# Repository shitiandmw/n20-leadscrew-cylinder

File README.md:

# n20-leadscrew-cylinder

**A 3D-printable linear actuator for a model excavator that looks like a hydraulic cylinder.** It is driven by a standard N20 gearmotor with an integrated M3 leadscrew, used exactly as bought. That is the actuator_v5 design described below; the current [two-wire V6](actuator_v6/README.md) (rev 6.2) uses the 12 V 1:50 N20 with an M4 × 0.7 leadscrew.

**The [complete X1 excavator](excavator_complete/README.md) puts the current revision of every subsystem together.** It combines:
- the J9 tracks and the X1 revision F X-frame;
- the RU66 slewing ring and the R3 turntable;
- body B1 rev B with the main board rev B (all seven motor drivers on the 12 V battery);
- the R12 arm.

It has an offline 3D demonstration with a scripted work cycle (travel, dig, swing, dump), the assembly order, an exploded view, layer-by-layer structure and the harness. Whole-machine checks cover clashes, the swing envelope, static balance, every cable's route over the arm's poses and the assembly moves that only exist on the combined machine. R12 sits on a new adapter, B01X, which replaces the ARM60 base on the turntable and now carries the arm cables. The folder also holds the whole machine's [wiring](excavator_complete/WIRING.md), [connector catalogue](excavator_complete/CONNECTORS.md) (every connector by type and model, with realistic models and a [gallery](excavator_complete/connector_gallery.html)), [standard parts and where they sit](excavator_complete/STANDARD_PARTS.md), [parts list](excavator_complete/BOM.md), [installation sequence](excavator_complete/ASSEMBLY.md) (animated in the viewer) and the [control circuit check](excavator_complete/CONTROL_CHECK.md).

The latest lower chassis is [X1 revision F with J9 tracks](track_wheel_jgy370/X1/README.md). Each X-frame leg ends in a curved support seated in a shallow recess in the track's main plate, clamped by two M4 screws through plain holes with the washers and nuts outside the plastic. The idler spring is enclosed in a bore in the track's main web and guided by a sliding piston. See the [revision notes](track_wheel_jgy370/X1/REV_F_NOTES.md) for the matched parts, assembly order and validation scope. To build the two tracks, start with the [track kit](track_wheel_jgy370/J9/TRACK_KIT.md): every file to print, every standard part to buy, the tools, an offline [installation animation](track_wheel_jgy370/J9/install_animation.html) that fits the parts step by step, and a [parts showcase](track_wheel_jgy370/J9/parts_showcase.html) to look at each part in 3D with its dimensions and material.

The [Sand / Lab application](excavator_app/README.md) turns the complete X1 / J9 / R12 machine into a Docker-deployable digging sandbox, with the R12 bucket's own profile doing the digging. A desktop displays the complete CAD assembly and a live sand yard: a deformable sand bed that slumps to its angle of repose, a load in each bucket that heaps up to the bucket's rated heaped capacity and slides off when the bucket is tipped, and falling sand wherever it spills or pours; a phone pairs by QR code and controls the boom, stick, bucket, slew and tracks over WebSocket. It includes touch joysticks, keyboard controls, emergency stop, connection watchdogs, and verified scoop-and-pour physics. Run `docker compose up --build -d` from `excavator_app/` to start it.

The [complete tracked arm60 excavator](excavator_60mm/README.md) adds independent track drives, steel-pinned links, sprung idlers, bearing-supported geared slewing and a recessed slew cover around the existing 60 mm arm. Its R3 upper body follows the Cat 320 layout: cab front-left, tank housing and stepped toolbox front-right, an engine hood with a battery hatch, and a curved counterweight on the 189 mm tail-swing radius holding steel ballast. Two 18650 cells sit in a cradle sized from manufacturer datasheets. Track R4 adds Berco-referenced sprockets engaging steel bushings, rollers with two outer guide flanges, and a 394 mm track stance around the 308 mm upper platform. Offline playback shows the loaded contact simulation, including passive wheel rotation, idler take-up, forward/reverse travel and braking. The preview allows independent boom and slew travel; track clearance is managed by the operator. Its folder includes parametric CAD, printable parts, a complete STEP assembly, an offline preview, mechanical assembly instructions and reproducible geometry, load and physics simulations. Physical fit, powered operation and payload still require prototype testing.

The [R10 arm with two boom actuators and a deeper boomerang profile](excavator_arm_dual/README.md) implements the user's latest revision: symmetric boom drives at Y = ±50 mm and a hollow, tapered boom with a 76.7 mm middle section, retaining the original joint coordinates and five replaceable teeth. All four actuators are modeled independently. Fixed-base rigid-body simulations track both unloaded and 150 g cycles under an assumed 100 N limit per drive; each boom drive peaks at 58.4 N with the example load. CAD, printable parts, assembly instructions, an offline viewer and a 54-second motion video are included. A feedback-offset case demonstrates unequal load sharing; hardware synchronization, structural strength and soil interaction remain unverified.

R6–R9 and their motion-review files have been removed from the workspace at the user's request. The current arm is R10 in `excavator_arm_dual/`, with actuator dependencies in `actuator_v6/`. Earlier tracked designs remain in Git history. The complete vehicle and sandbox still use the earlier ARM60 model; R10 has not been integrated into them.

The 1:12 ground-mounted arm (`excavator_arm/`, with its V6-T/B/K actuators) and the J8 track at the top of `track_wheel_jgy370/` were removed on 2026-11-12 because nothing current used them. They remain in Git history; for example, commit `39bc9a7` has both.

A separate [60 mm stroke edition](excavator_arm_60mm/README.md) uses four identical actuators and smaller 1:15 proportions: 380 mm boom, 193.3 mm stick and 80 mm bucket. Its [offline preview](excavator_arm_60mm/3D_preview.html), CAD and drawings are kept in their own folder. Its actuator, V6-U60, is one of the three lengths (V6-S, V6-U60, V6-L) of the general-purpose [two-wire V6 actuator](actuator_v6/README.md). The current R4 model integrates the upper lift mounts into broad supports on the boom, with thicker cheeks and a shared steel cross-pin.

The motor's own leadscrew drives a brass nut inside the rod. Two Hall-effect end stops hide in a covered channel along the barrel. A small controller blocks each direction in hardware once that end is reached.

The geometry, STL/STEP files, wire routes, schematic and a self-contained 3D preview are all generated from parametric Python (CadQuery).

> **Status:** the design is complete and checked in CAD, but it has not been printed or powered yet. See [Status](#status).

## Features

- **Unmodified N20 leadscrew motor.** There is no coupler, bearing or separate screw. The brass M3 nut in the rod's carrier rides directly on the motor's screw. The gearbox seats on a step in the barrel and the rear cap backs the motor can.
- **Hydraulic-cylinder look:**
  - a round Ø21 mm yellow barrel;
  - Ø23 mm graphite end caps, with a wiper lip at the rod end;
  - a Ø9 mm chrome-look rod;
  - Ø14 mm clevis eyes for Ø3 mm pins;
  - a hose-style cable port with a TPU boot.
- **Hidden end stops.** Two DRV5033AJ Hall sensors sit in a dovetail channel under a flush cover strip, along with their resistors, capacitors and wiring. Each sensor slides ±3 mm for calibration.
- **Hardware direction gating.** A 74HC08 blocks motion toward an end as soon as that end's sensor trips, regardless of the firmware. The Arduino adds a current trip (ACS712), a 30 s run timeout and latching faults.
- **Parametric.** Change the leadscrew length and the stroke, barrel, rod, sensor positions, cover strip and wire routes all follow.
- **Self-checking outputs.**
  - The CAD build checks for interference over the full stroke, checks that every wire lands on its terminal, and checks that every STL is watertight.
  - The schematic generator rebuilds the connections from the drawing itself. It compares them with the netlist and with the firmware's pin constants.

## Specifications

Default build, for a 40 mm leadscrew:

| | |
|---|---|
| Stroke | 30 mm, plus 2 / 3 mm mechanical over-travel at retract / extend |
| Pin centres | 108 mm retracted → 138 mm extended |
| Barrel | Ø21 × 76 mm, end caps Ø23 mm |
| Rod | Ø9 mm |
| Clevis eyes | Ø14 mm, 10.4 mm thick, Ø3.2 mm holes |
| Motor | N20 gearmotor (10 × 12 mm body) with integrated M3 × 0.5 leadscrew |
| End stops | 2 × TI DRV5033AJQLPG and an N35 Ø4 × 2 mm magnet |
| Electronics | 6 V motor supply, 5 V logic: DRV8833, ACS712-05B, SN74HC08, Arduino Nano |

A longer screw gives a longer stroke. For example, a 60 mm screw gives 50 mm of stroke and 128 → 178 mm pin centres. See the [full table](actuator_v5/README.md#rebuild).

## A look inside

The left image is a section on the pin plane, showing the motor, leadscrew, brass nut in the rod's carrier, and magnet. The right image shows the sensor channel with the cover strip removed.

For an interactive view, download [`actuator_v5/3D_preview.html`](actuator_v5/3D_preview.html) and open it in any browser. It is a single 7 MB file that works offline; GitHub can't run it in the page. The preview includes:

- exterior, section, wiring and core-part views;
- a stroke slider;
- a live demo of the end stops and the overcurrent trip.

## Electronics

| Sheet 1: inside the actuator | Sheet 2: controller board |
|---|---|
|  |  |

- Full schematic: [`schematic.pdf`](actuator_v5/electronics/schematic.pdf) (A3).
- Harness, pin tables and commissioning: [`wiring.md`](actuator_v5/electronics/wiring.md).
- Firmware: [`actuator_protection.ino`](actuator_v5/electronics/actuator_protection/actuator_protection.ino).

## Repository layout

```
actuator_v5/
├── README.md           build guide: print settings, assembly order, calibration, rebuild
├── BOM.md              everything to buy, with reference designators
├── 3D_preview.html     offline interactive 3D viewer
├── stl/                printable parts (PETG); soft/ = TPU boot; fit_samples/ = test slices
├── step/               single parts plus the full assembly with wiring
├── electronics/        schematic, netlist, wiring.md, Arduino sketch, logic tests
├── images/             renders and analysis plots
├── references/         motor drawing and photo the design is based on
├── parameters.json     key dimensions of the current build
├── validation.json     geometric check report
└── source/             generators (CadQuery, schemdraw, Blender, three.js viewer)
```

## Building one

1. **Measure your leadscrew** from the gearbox front face to the tip. If it is not 40 mm, rebuild with `--screw-length` (see below).
2. **Print** the parts in `actuator_v5/stl/` in PETG and the boot in `stl/soft/` in TPU 95A. Print the four fit samples first.
3. **Buy** the parts in [`BOM.md`](actuator_v5/BOM.md).
4. **Assemble, wire and calibrate** by following the [build guide](actuator_v5/README.md#assembly-order). Check the motor direction first. Then set each Hall sensor so that it stops the motor just before the mechanical stop.

## Rebuilding from source

Tested with Python 3.11 and the packages in [`requirements.txt`](actuator_v5/source/requirements.txt) (CadQuery 2.8, trimesh, schemdraw, matplotlib, ReportLab, PyMuPDF). The renders need Blender 4.2.

```sh
cd actuator_v5
pip install -r source/requirements.txt
python source/build_v5.py --screw-length 40         # STEP/STL, meshes, validation (about 3 minutes)
python source/magnet_trigger.py                     # magnet model and Hall placement
python source/build_schematic.py                    # schematic, plus connectivity and firmware checks
python source/build_viewer.py                       # 3D_preview.html
blender -b -P source/render_v5.py -- --out images   # optional renders
```

`build_v5.py` stops with an error if any geometric check fails.

The logic tests need no hardware (run them from `actuator_v5/` too):

```sh
python electronics/check_direction_gates.py         # 74HC08 gates: all 16 input states
c++ -std=c++17 -UNDEBUG electronics/protection_logic_test.cpp -o /tmp/protection_test && /tmp/protection_test
```

## Status

Checked:

- **CAD** (results in [`validation.json`](actuator_v5/validation.json)):
  - no interference between parts, hardware and wires anywhere in the stroke;
  - all eight wires land on their terminals;
  - wire routes still clear with each sensor moved ±3 mm;
  - every STL is watertight.
- **Electronics:**
  - the schematic's connections match the netlist and the firmware's pin map;
  - the 74HC08 truth table passes;
  - the protection-logic unit test passes;
  - the Arduino sketch compiles against a stub of the Arduino API.

Not verified yet:

- printing and fit;
- the real motor's ratings, the gearbox's axial load capacity and PETG creep under load;
- magnetic switching on real parts (the magnet model ignores the steel screw and nut);
- the firmware running on a board.

The current trip (550 mA for 150 ms) is a starting value. Set it against the real motor during commissioning.

To do:

- the remaining renders (stroke positions and close-ups);
- an illustrated assembly guide PDF.

## License

No license has been chosen yet. The bundled three.js is MIT-licensed (see [`THREE_LICENSE.txt`](actuator_v5/source/vendor/THREE_LICENSE.txt)).

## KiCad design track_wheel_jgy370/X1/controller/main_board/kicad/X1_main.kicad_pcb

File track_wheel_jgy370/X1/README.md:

# X1 revision F — straight arms seated in the track main beam

Each X101 arm runs straight at its full 28 mm width into the track main plate and ends flat in a plain 1.5 mm recess. The deck and the arched underside are single smooth curves. One screw on each side of the arm's centre web clamps the joint through plain holes; the heads and washers sit in side slots under the closed deck, and the rear washers and nuts are external. The accepted enclosed spring guide is retained.

The R3 turntable sits on the RU66 seat, and the upper body B1 rev B sits on it. The body is traced from the Cat 320: three main prints (counterweight, left half with the cab, right half with the tank), four small ones, and the 18650 battery on the swing centreline under a lift-off hatch. Rev B issue 2 (2026-11-07) adds a cable notch in each half's inboard hood wall for the arm harness of the complete machine (`excavator_complete/WIRING.md`). See [TURNTABLE.md](TURNTABLE.md) and [BODY.md](BODY.md).

**Control system: spec C1 issue 4; main board rev B designed (schematic, PCB and firmware).**
- The main board (rev B) sits in the left bay: ESP32-S3, 7 × DRV8876 on the battery, 5 V / 3.3 V rails, lamps, buzzer and an expansion header. Its motor, lamp and expansion headers are top entry since 2026-11-14, so the plugs go on from above.
- Its KiCad 9 schematic is complete and checked: ERC clean, and KiCad's netlist matches the source netlist pin for pin. The BOM uses verified LCSC parts.
- The 4-layer, 96 × 64 mm PCB is routed. KiCad's DRC finds no errors and no unconnected items, and the board matches the schematic. Gerbers, drill files, BOM and CPL for JLCPCB are in `controller/main_board/fab/`; nothing has been ordered. See [controller/main_board/DESIGN.md](controller/main_board/DESIGN.md).
- Its firmware (`controller/firmware/`) compiles for the ESP32-S3 and its logic tests pass; it has not run on hardware.
- The board is modelled in the body CAD from its layout, and the body checks pass ([BODY.md](BODY.md)).
- **Plain-language guide:** [controller/X1_controller_guide.html](controller/X1_controller_guide.html) explains the board, the program and the installation with pictures, animations and a simulator of the firmware's rules. Open it in a browser; it works offline. It is built by `controller/source/build_guide.py`.
- The handle is parked; only its ESP-NOW link and control behaviour are fixed. The later 4G remote is deferred.
- Requirements: [controller/SPEC.md](controller/SPEC.md) and `controller/X1_control_spec_C1.pdf`.

## Open the current model

- [3D_preview.html](3D_preview.html) is an offline interactive viewer. Select **Track connections**, **X-frame only** or **Spring guides** for the chassis, and **Body B1**, **Cab and operator**, **Inside the body** or **Body off for service** for the upper body.
- [step/X1_crawler_chassis.step](step/X1_crawler_chassis.step) contains the complete coloured chassis and both tracks.
- [step/X1_turntable_assembly.step](step/X1_turntable_assembly.step) contains the revised X101, retained R3 turntable and fixed ARM60 pivot base. The moving arm shown in the viewer is a reference model; it is not embedded in this STEP.
- [step/X1_body_assembly.step](step/X1_body_assembly.step) contains the body B1 prints (B101–B107), their hardware and electronics.
- [X1_arc_mount_detail.pdf](X1_arc_mount_detail.pdf) shows sections taken from the exported CAD.
- [X1_layout.pdf](X1_layout.pdf) is the plan, front section and turntable-seat layout with the Cat 320 reference table.
- [ASSEMBLY.md](ASSEMBLY.md), [BOM.md](BOM.md) and [REV_F_NOTES.md](REV_F_NOTES.md) describe the current connection.

Use the revision F X101, J901 and J909 parts together. X1 supplies the mirrored right J901 and J909; their left counterparts are in J9.

## Connection geometry

The four joints are centred at X ±63.5. Each arm is 28 mm wide and straight from vehicle Y ±96 to its end at Y ±137.5. Its deck falls in one curve from Z85 at the carbody to Z74 at the plate; its underside arches from the carbody rim (Z34) to a crown at Z57.5 over the motor pod, then curves down to Z53 at the plate. The flat 28 × 21 mm end (Z53–74) is the contact face.

The receiving seat is a plain rectangle, 1.5 mm deep from the original main-plate face at local Y−34 to Y−32.5, with 0.15 mm side clearance and an open top. The plate's inner surface remains at Y−24, leaving 8.5 mm behind the recessed contact face. The joints mate at vehicle Y ±137.5. Mechanism recesses retain the original motor, roller and yoke positions.

Each joint uses two horizontal M4 × 25 ISO 4762 socket screws, with one Ø9/Ø4.4 × 0.8 mm washer beneath each head and each external M4 nut. The heads sit in side slots (Z62.75–72.75, vehicle Y ±97 to ±127) either side of a 9 mm centre web, with 10.5 mm of arm stock clamped between the washer face and the seat. There are no mounting screw-head counterbores or recessed nut pockets. The front screw axes are X54 and X73, with mirrored rear positions, all at Z67.75.

Through the slots the arm section is a closed deck, a 9 mm web and a full-width base. Arm section properties are recorded in [revf_leg_sections.json](revf_leg_sections.json) as geometry only. Printed fit, root bending capacity, fastener preload retention, creep and strength still require physical testing. The cosmetic housing is relieved around the arm with about 0.5 mm clearance (0.41 mm measured minimum) and carries no chassis load.

## Accepted spring and retained mechanisms

The spring guide keeps its Ø16.4 bore, Ø21.2 exterior and 8 mm recessed seat. The J908 yoke retains its Ø15.6 piston. Fitted spring length is 25.8 mm and recoil is 4.2 mm, with approximately 77 N nominal preload. Use the matching guide and yoke, and check clean, free movement through the whole stroke.

Track centres remain 340 mm apart, shoe width is 70 mm and overall shoe width is 410 mm. The chassis retains the THK RU66 seat at Z85, turntable mounting face at Z100, Ø25 centre passage, belly cover and R3 upper drive. See [TURNTABLE.md](TURNTABLE.md) and the [bearing reference](references/thk_ru66/SOURCE.md).

The older R3 swing playback concerns the upper drive. It does not establish revision F chassis strength.

## Printing and assembly

X101 remains one part, printed with its bearing seat on the bed. Its current print bounds are **155 × 275 × 51 mm**; check printer capacity against `revf_part_exports.json`. In this inverted orientation, the arm decks and the head-slot roofs need support; keep scars off the arm end faces, receiving seats and washer faces. No split-frame design is supplied.

Install the road and support rollers with their axles, the motor and housing first. Hold both tracks at their final spacing and lower the bare X101 frame vertically into their open-top receiving seats; sideways fitting clashes with the motor and housing. Leave the rear sprocket and chain off. Slide each screw and washer sideways into its head slot and push it through; a compact 7 mm nut-holding tool holds the external nut while a 3 mm L-key, handle out of the slot, turns the screw. Fit the sprocket and chain after tightening. Follow [ASSEMBLY.md](ASSEMBLY.md) for the fitting sequence and tool route. For later service, prepare the affected track as specified in ASSEMBLY.md, lower it at least 80 mm relative to the independently supported chassis, then slide it outward.

The print list and standard parts for both tracks are in [J9/TRACK_KIT.md](../J9/TRACK_KIT.md), with an offline [installation animation](../J9/install_animation.html) whose "Both on X101" mode shows this joint step, and a [parts showcase](../J9/parts_showcase.html) with every part's dimensions and material.

Use fit samples for the arm end in its seat, the through-holes and the spring piston before complete prints. No material, infill, layer orientation, payload or tightening torque has been physically qualified.

## Verification and rebuilding

All reports below are computed fresh on the delivered revision F files; none inherit results from earlier designs.

| Report | What it checks |
|---|---|
| [arc_seat_mount_validation.json](arc_seat_mount_validation.json) | Joint seating and contact, fasteners, key and socket access, vertical frame fitting and track service routes, sprocket fitting, idler recoil, chain phases, upper swing, RU66 seat and belly-cover screw access, clearances |
| [../J9/validation.json](../J9/validation.json) | Every track trial: static fit, drive rotation, idler travel and stop, spring at recoil, chain phases, assembly paths and tools; spring envelope and main-plate seat clearances; the drive coupling against the seller drawing; the chain joints (J910 revision B: neighbouring links, screw heads, nuts and seat bosses against the roller flanges, the sprocket between the ears) |
| [revf_part_exports.json](revf_part_exports.json) | The ten changed STEP/STL designs (X101, both J901, both J909, J902, J904, J906, J908, J910) match the current source, are single solids and watertight meshes; X101 fills its required envelope |
| [revf_refresh_validation.json](revf_refresh_validation.json) | The three STEP assemblies and both viewer scenes hold the current parts, the joint hardware, the drive group (J902 on its flange coupling) and the chain (J910 revision B shoes, each joint with its M3 × 60 screw, sleeve and nyloc nut), with no parts of the old hub or the old pin joints left |
| [revf_leg_sections.json](revf_leg_sections.json) | Arm cross-section properties (geometry only, not a strength check) |
| [turntable_validation.json](turntable_validation.json) | The R3 turntable on the revision F chassis: fits, assembly paths, tools and the swing envelope |
| [body_validation.json](body_validation.json) | The body B1 on the turntable: fits, the swing sweep over the tracks, assembly and service paths, tools, clearances |
| [browser_validation.json](browser_validation.json) | The offline viewer and its screenshots |

Primary source files are `source/x1_parts.py`, `../J9/source/j9_mounts.py` and `../J9/source/j9_parts.py`. Run from `source/` with CadQuery and the original repository (it supplies `track_wheel/source`):

```sh
python export_arc_frame.py                     # X101 STEP/STL
python ../../J9/source/export_revf_track.py    # left and mirrored right J901/J909
(cd ../../J9/source && python -c "import build_j9 as B, j9_parts as P; B.export_parts({n: dict(shape=P.PRINTED[n][0](), color=P.PRINTED[n][1], quantity=P.PRINTED[n][2], material=P.PRINTED[n][3], note=P.PRINTED[n][4]) for n in ('J902_sprocket', 'J904_roller', 'J906_idler_wheel', 'J908_U_yoke', 'J910_track_shoe_70')})")   # J902/J904/J906/J908/J910 STEP/STL
python check_revf_exports.py                   # verify the ten parts against the source
python refresh_revf.py                         # rebuild assemblies and scenes; --verify only checks them
python ../../J9/source/check_revf_track.py     # fresh J9 track validation
python check_arc_sections.py
python draw_arc_mounts.py                      # X1_arc_mount_detail.pdf
python check_arc_seat_mounts.py                # joint acceptance (long; resumes from checkpoints)
python draw_layout.py                          # X1_layout.pdf
python package_revf.py                         # review PDF, ZIP and manifest in ../../../output
```

`build_x1.py` is now a helper library for the exporter and the turntable builder. Its own `main()` predates the revision F joint and refuses to run.

The turntable, the body and the swing simulation sit on top of the chassis. Rebuild them after a chassis change, in this order:

```sh
python build_body.py mass                            # body masses, used by the turntable mass stage and the simulation
python build_turntable.py                            # turntable STEP/STL, turntable_validation.json, mass properties, viewer data (long)
python build_body.py export static sweep paths tools clearances final   # body STEP/STL, body_validation.json (see BODY.md -> Rebuild)
python simulate_swing.py                             # ../simulation/turntable_swing_*.json (MuJoCo)
python draw_swing_report.py                          # ../X1_turntable_simulation.pdf
python build_viewer.py                               # ../3D_preview.html, with the turntable, the body and the swing traces
node check_viewer.cjs                                # screenshots + browser_validation.json (NODE_PATH must contain playwright)
```

STEP/STL files and the offline viewers work on their own; rebuilding is only needed after a design change.

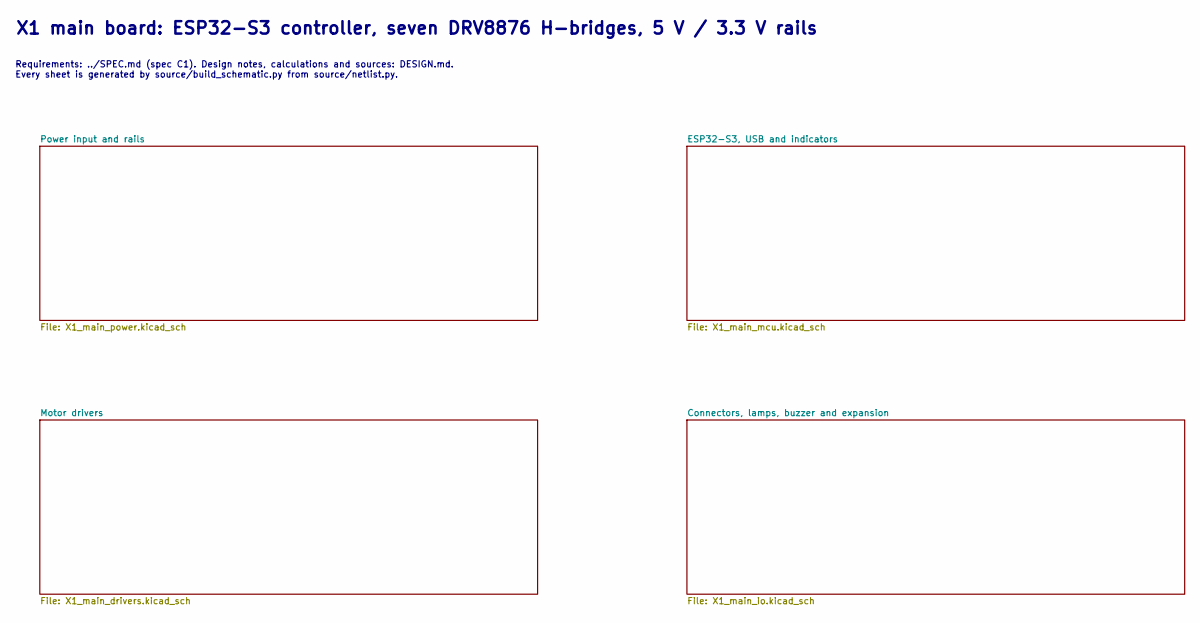
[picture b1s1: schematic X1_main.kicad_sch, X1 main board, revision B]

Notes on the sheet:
X1 main board: ESP32-S3 controller, seven DRV8876 H-bridges, 5 V / 3.3 V rails
Requirements: ../SPEC.md (spec C1). Design notes, calculations and sources: DESIGN.md. Every sheet is generated by source/build_schematic.py from source/netlist.py.

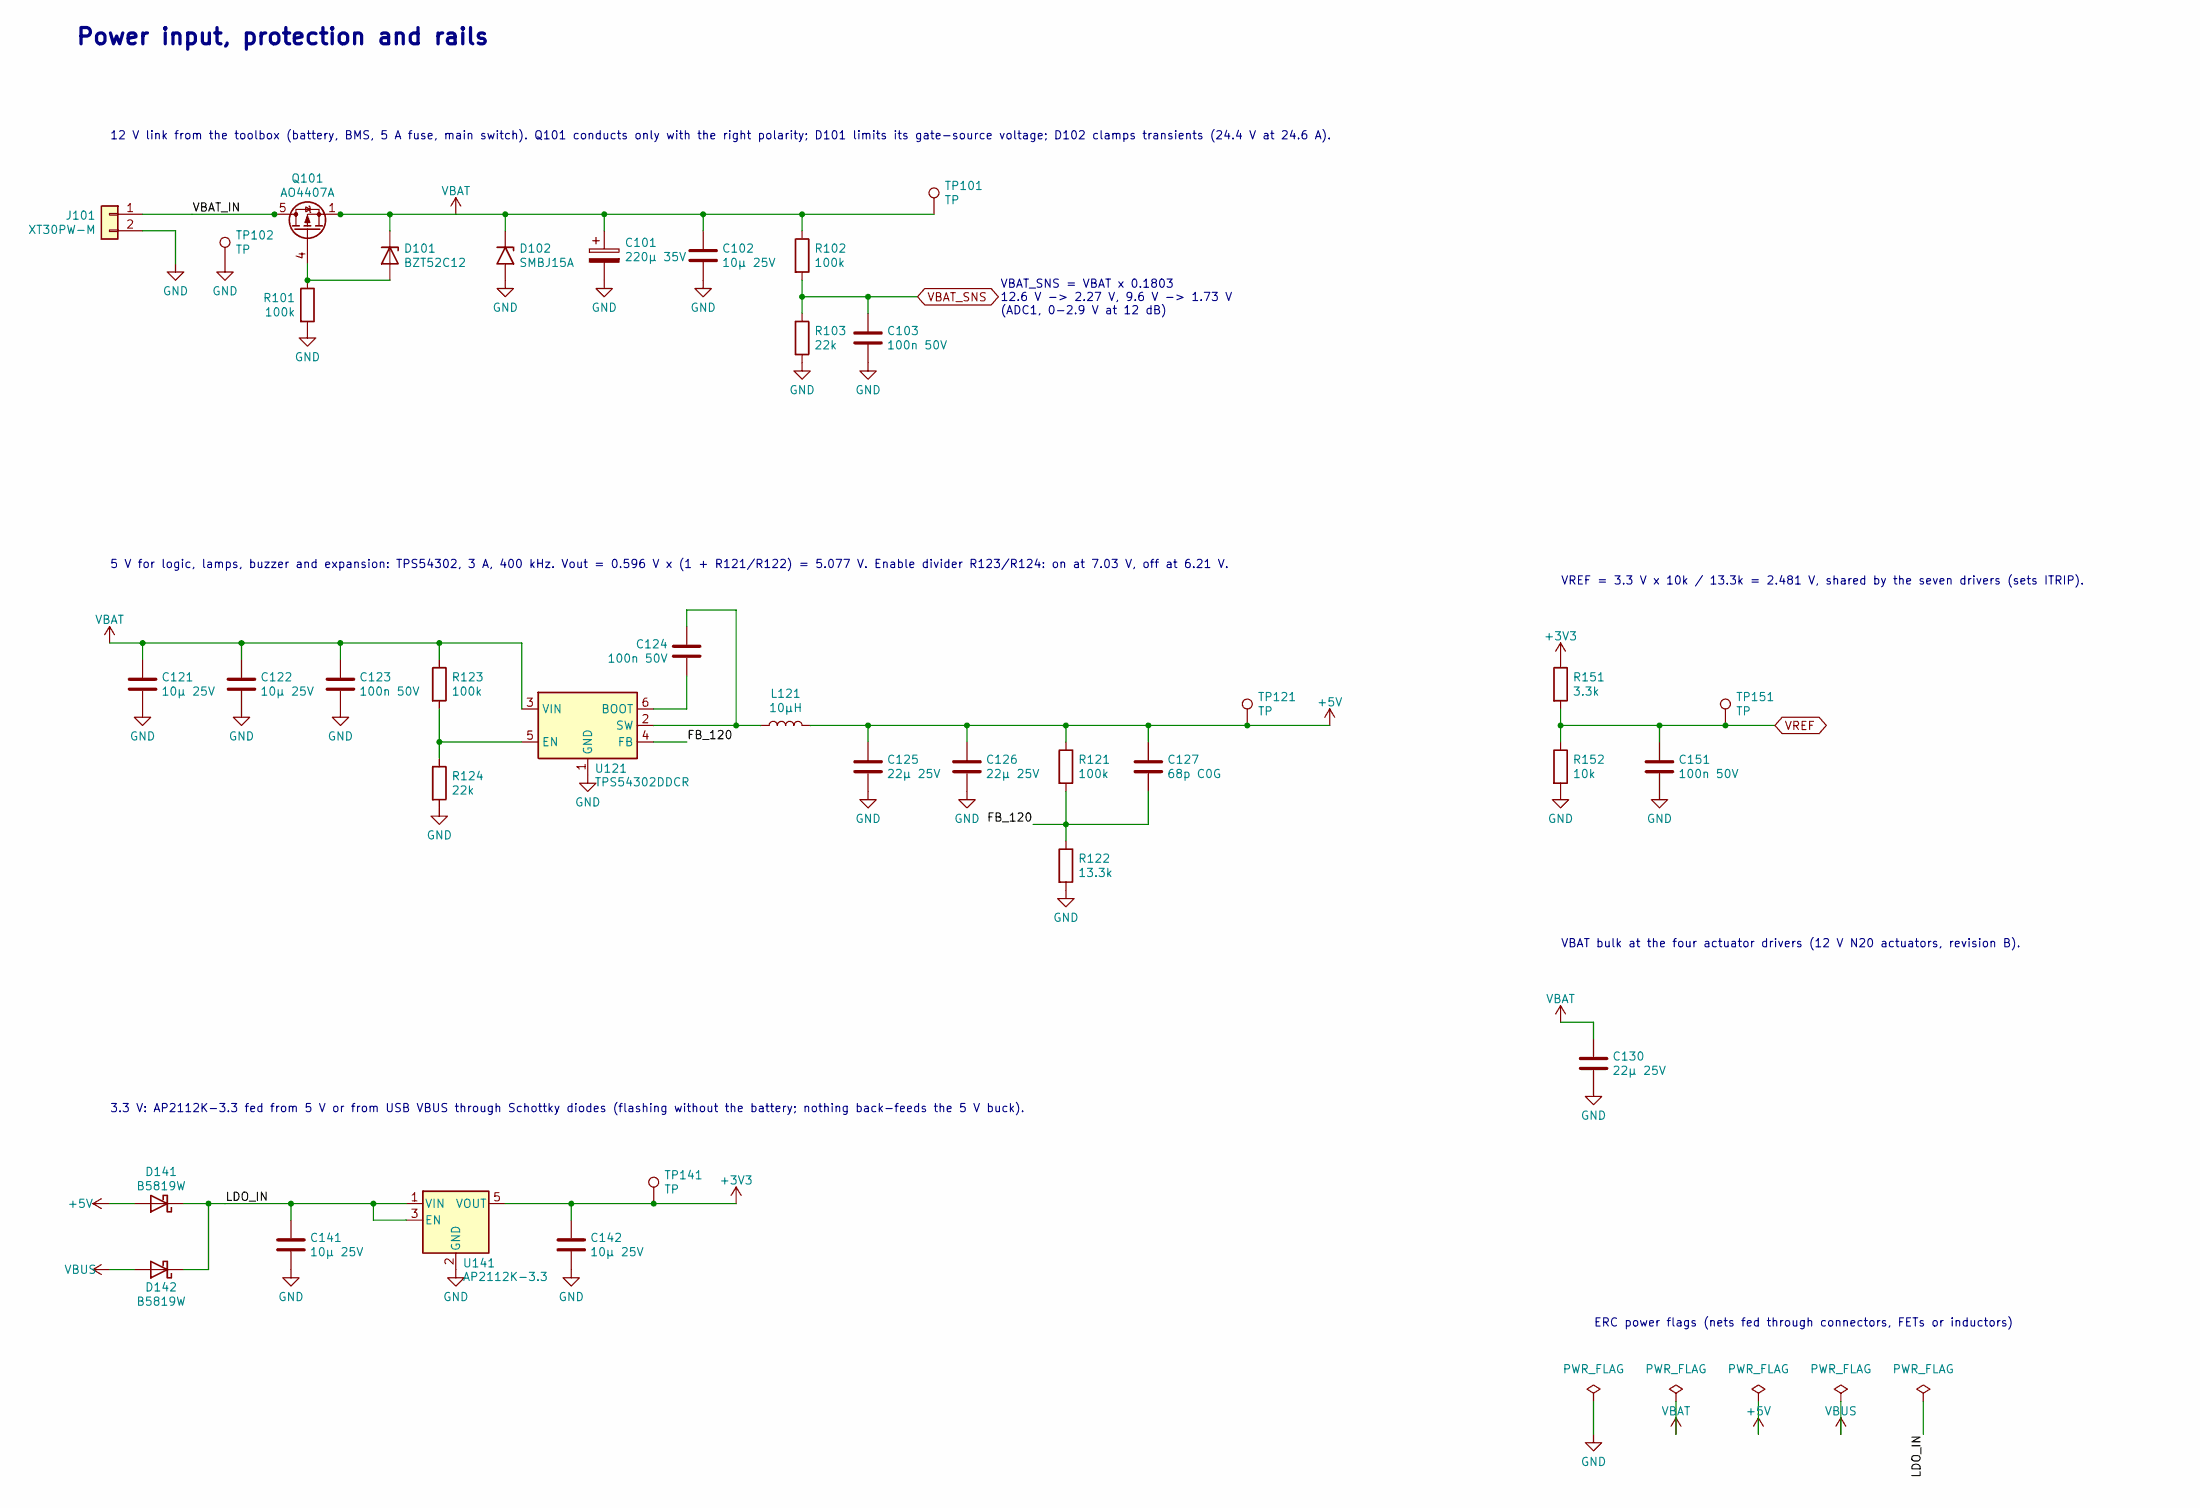
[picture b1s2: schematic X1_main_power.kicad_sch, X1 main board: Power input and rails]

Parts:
C101: 220µ 35V; CP_Elec_8x10.5; MPN Nichicon UCD1V221MNL1GS; LCSC C136294
C102, C121, C122, C141, C142: 10µ 25V; C_0805_2012Metric; MPN Samsung CL21A106KAYNNNE; LCSC C15850
C103, C123, C124, C151: 100n 50V; C_0603_1608Metric; MPN Yageo CC0603KRX7R9BB104; LCSC C14663
C125, C126, C130: 22µ 25V; C_1206_3216Metric; MPN Samsung CL31A226KAHNNNE; LCSC C12891
C127: 68p C0G; C_0603_1608Metric; MPN Samsung CL10C680JB8NNNC; LCSC C28262
D101: BZT52C12; D_SOD-123; MPN JSCJ BZT52C12; LCSC C43491
D102: SMBJ15A; D_SMB; MPN Littelfuse SMBJ15A (unidirectional); LCSC C83846
D141, D142: B5819W; D_SOD-123; MPN JSCJ B5819W SL; LCSC C8598
J101: XT30PW-M; AMASS_XT30PW-M_1x02_P2.50mm_Horizontal; MPN Amass XT30PW-M30.G.Y; LCSC C431092
L121: 10µH; L_Bourns_SRP6060FA; MPN Bourns SRP6060FA-100M; LCSC C2046759
Q101: AO4407A; SOIC-8_3.9x4.9mm_P1.27mm; MPN AOS AO4407A; LCSC C16072
R101, R102, R121, R123: 100k; R_0603_1608Metric; MPN UNI-ROYAL 0603WAF, 100k 1 %; LCSC C25803
R103, R124: 22k; R_0603_1608Metric; MPN UNI-ROYAL 0603WAF, 22k 1 %; LCSC C31850
R122: 13.3k; R_0603_1608Metric; MPN UNI-ROYAL 0603WAF, 13.3k 1 %; LCSC C25952
R151: 3.3k; R_0603_1608Metric; MPN UNI-ROYAL 0603WAF, 3.3k 1 %; LCSC C22978
R152: 10k; R_0603_1608Metric; MPN UNI-ROYAL 0603WAF, 10k 1 %; LCSC C25804
TP101, TP102, TP121, TP141, TP151: TP; TestPoint_Pad_D1.5mm; MPN test pad (copper only)
U121: TPS54302DDCR; SOT-23-6; MPN TI TPS54302DDCR; LCSC C311983
U141: AP2112K-3.3; SOT-23-5; MPN Diodes AP2112K-3.3TRG1; LCSC C51118

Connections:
+3V3: C142.1, R151.1, TP141.1, U141.5 (VOUT); also elsewhere on the board
+5V: C125.1, C126.1, C127.1, D141.2 (A), L121.2, R121.1, TP121.1; also elsewhere on the board
/Power input and rails/FB_120: C127.2, R121.2, R122.1, U121.4 (FB)
/Power input and rails/LDO_IN: C141.1, D141.1 (K), D142.1 (K), U141.1 (VIN), U141.3 (EN)
/Power input and rails/VBAT_IN: J101.1, Q101.5 (D), Q101.6 (D), Q101.7 (D), Q101.8 (D)
GND: C101.2, C102.2, C103.2, C121.2, C122.2, C123.2, C125.2, C126.2, C130.2, C141.2, C142.2, C151.2, D102.2 (A2), J101.2, R101.2, R103.2, R122.2, R124.2, R152.2, TP102.1, U121.1 (GND), U141.2 (GND); also elsewhere on the board
unnamed: D101.2 (A), Q101.4 (G), R101.1
unnamed: C124.1, U121.6 (BOOT)
unnamed: R123.2, R124.1, U121.5 (EN)
unnamed: C124.2, L121.1, U121.2 (SW)
VBAT: C101.1, C102.1, C121.1, C122.1, C123.1, C130.1, D101.1 (K), D102.1 (A1), Q101.1 (S), Q101.2 (S), Q101.3 (S), R102.1, R123.1, TP101.1, U121.3 (VIN); also elsewhere on the board
VBAT_SNS: C103.1, R102.2, R103.1; also elsewhere on the board
VBUS: D142.2 (A); also elsewhere on the board
VREF: C151.1, R151.2, R152.1, TP151.1; also elsewhere on the board

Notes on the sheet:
Power input, protection and rails
12 V link from the toolbox (battery, BMS, 5 A fuse, main switch). Q101 conducts only with the right polarity; D101 limits its gate-source voltage; D102 clamps transients (24.4 V at 24.6 A).
VBAT_SNS = VBAT x 0.1803 12.6 V -> 2.27 V, 9.6 V -> 1.73 V (ADC1, 0-2.9 V at 12 dB)
5 V for logic, lamps, buzzer and expansion: TPS54302, 3 A, 400 kHz. Vout = 0.596 V x (1 + R121/R122) = 5.077 V. Enable divider R123/R124: on at 7.03 V, off at 6.21 V.
3.3 V: AP2112K-3.3 fed from 5 V or from USB VBUS through Schottky diodes (flashing without the battery; nothing back-feeds the 5 V buck).
VREF = 3.3 V x 10k / 13.3k = 2.481 V, shared by the seven drivers (sets ITRIP).
VBAT bulk at the four actuator drivers (12 V N20 actuators, revision B).
ERC power flags (nets fed through connectors, FETs or inductors)

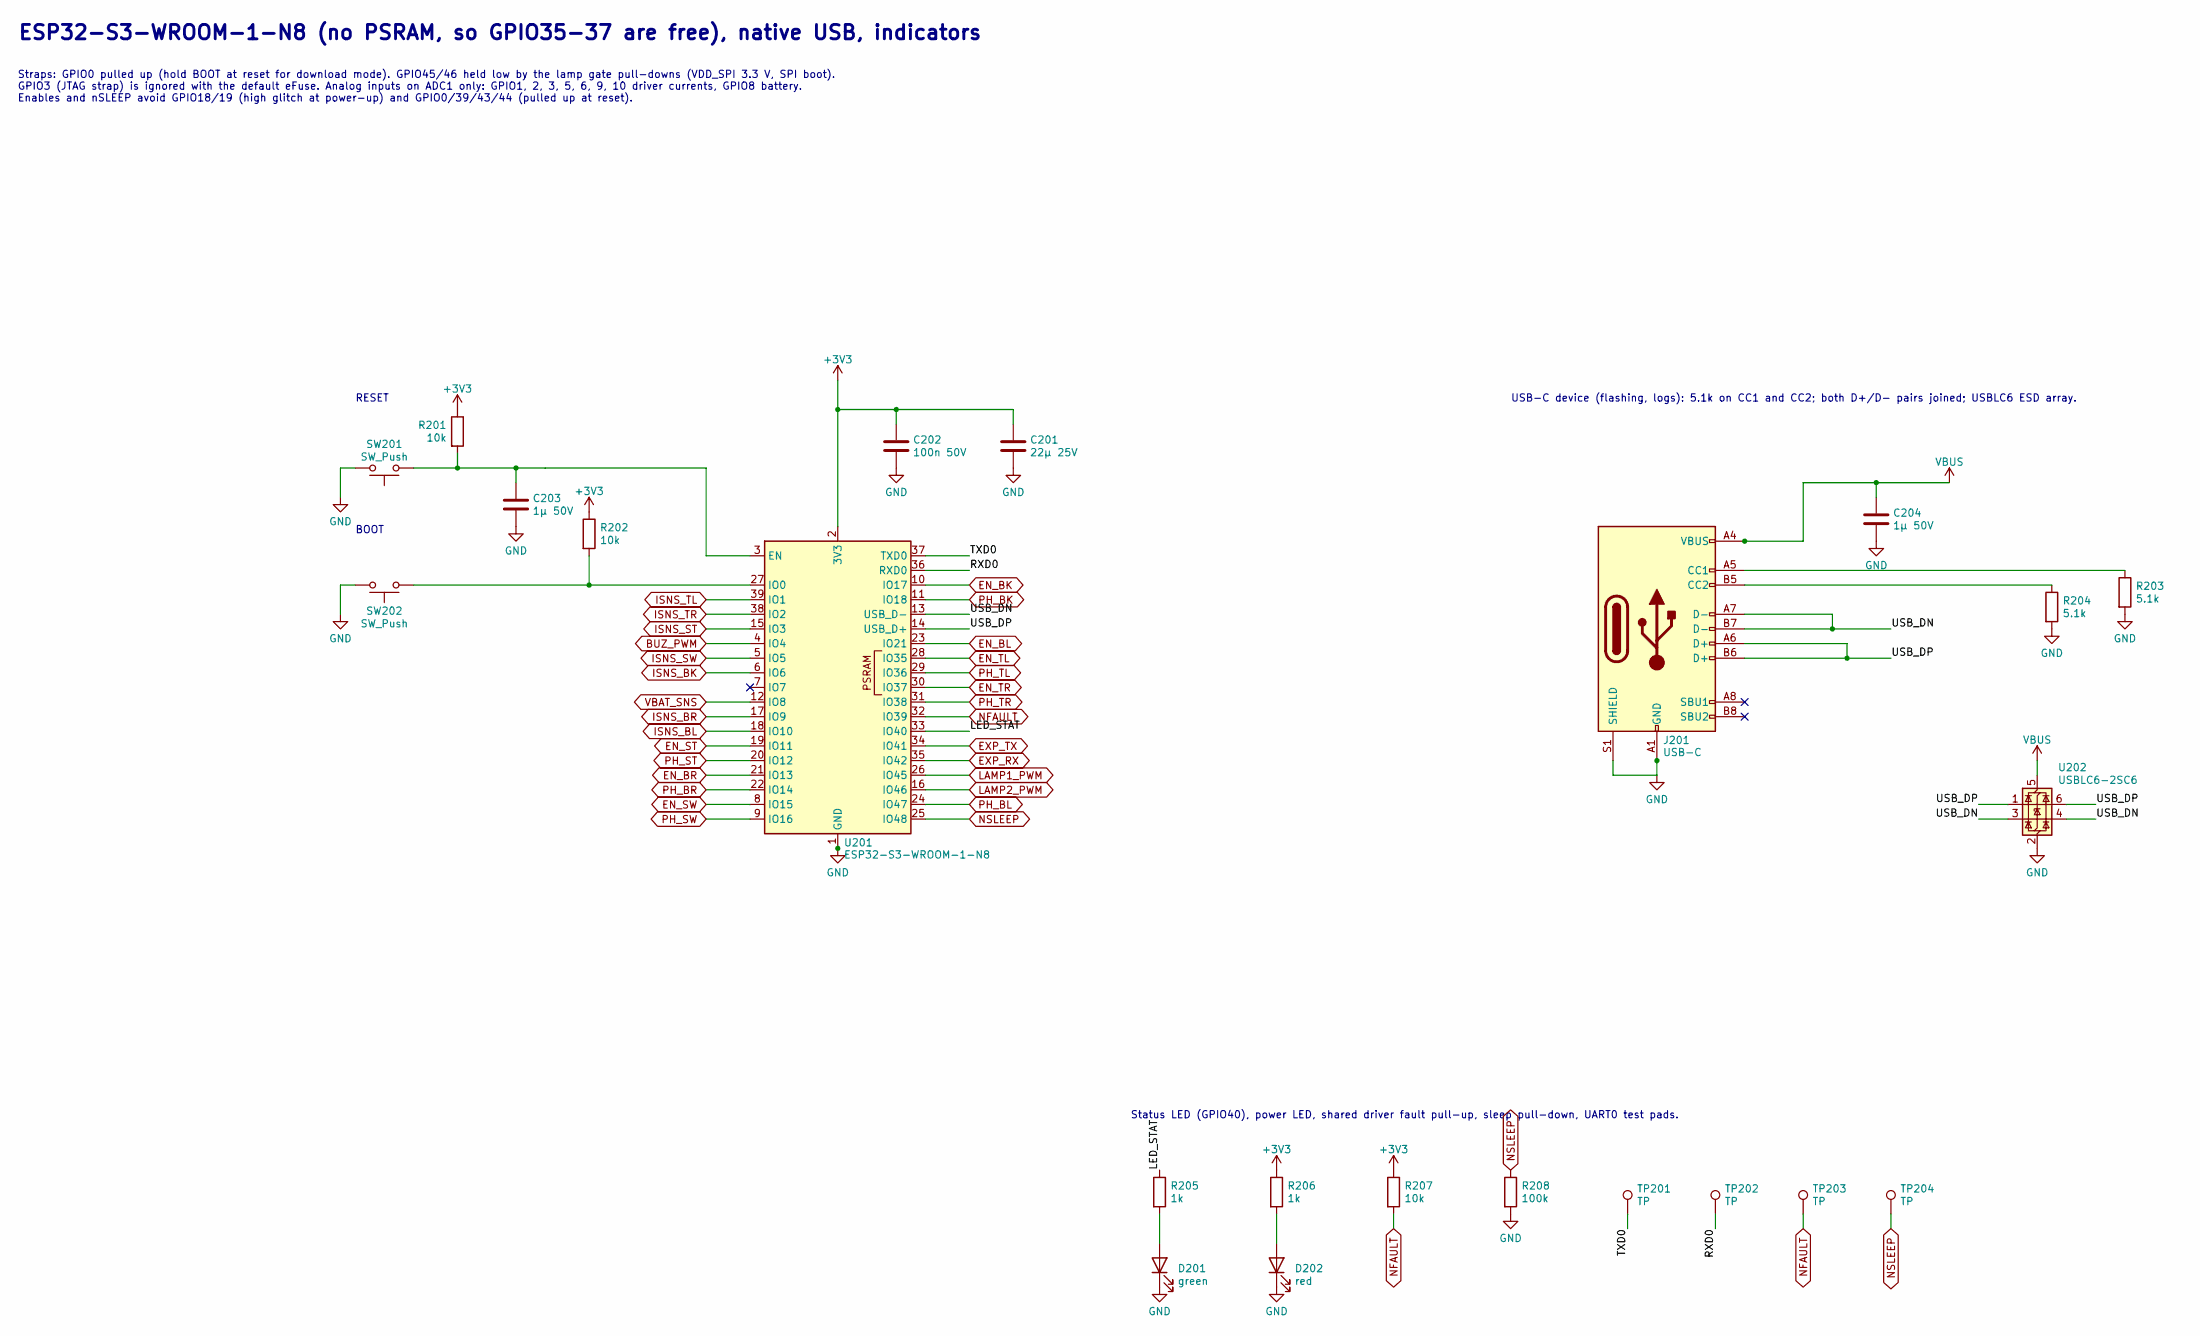
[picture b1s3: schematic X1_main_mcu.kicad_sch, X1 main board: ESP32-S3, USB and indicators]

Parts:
C201: 22µ 25V; C_1206_3216Metric; MPN Samsung CL31A226KAHNNNE; LCSC C12891
C202: 100n 50V; C_0603_1608Metric; MPN Yageo CC0603KRX7R9BB104; LCSC C14663
C203, C204: 1µ 50V; C_0603_1608Metric; MPN Samsung CL10A105KB8NNNC; LCSC C15849
D201: green; LED_0805_2012Metric; MPN Hubei KENTO KT-0805G; LCSC C2297
D202: red; LED_0603_1608Metric; MPN Hubei KENTO KT-0603R; LCSC C2286
J201: USB-C; USB_C_Receptacle_HRO_TYPE-C-31-M-12; MPN Korean Hroparts TYPE-C-31-M-12; LCSC C165948
R201, R202, R207: 10k; R_0603_1608Metric; MPN UNI-ROYAL 0603WAF, 10k 1 %; LCSC C25804
R203, R204: 5.1k; R_0603_1608Metric; MPN UNI-ROYAL 0603WAF, 5.1k 1 %; LCSC C23186
R205, R206: 1k; R_0603_1608Metric; MPN UNI-ROYAL 0603WAF, 1k 1 %; LCSC C21190
R208: 100k; R_0603_1608Metric; MPN UNI-ROYAL 0603WAF, 100k 1 %; LCSC C25803
SW201, SW202: SW_Push; SW_Push_1P1T_XKB_TS-1187A; MPN XKB TS-1187A-B-A-B; LCSC C318884
TP201, TP202, TP203, TP204: TP; TestPoint_Pad_D1.5mm; MPN test pad (copper only)
U201: ESP32-S3-WROOM-1-N8; ESP32-S3-WROOM-1_X1; MPN Espressif ESP32-S3-WROOM-1-N8; LCSC C2913198
U202: USBLC6-2SC6; SOT-23-6; MPN ST USBLC6-2SC6; LCSC C7519

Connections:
+3V3: C201.1, C202.1, R201.1, R202.1, R206.1, R207.1, U201.2 (3V3); also elsewhere on the board
/ESP32-S3, USB and indicators/LED_STAT: R205.1, U201.33 (IO40)
/ESP32-S3, USB and indicators/RXD0: TP202.1, U201.36 (RXD0)
/ESP32-S3, USB and indicators/TXD0: TP201.1, U201.37 (TXD0)
/ESP32-S3, USB and indicators/USB_DN: J201.A7 (D-), J201.B7 (D-), U201.13 (USB_D-), U202.3 (I/O2), U202.4 (I/O2)
/ESP32-S3, USB and indicators/USB_DP: J201.A6 (D+), J201.B6 (D+), U201.14 (USB_D+), U202.1 (I/O1), U202.6 (I/O1)
BUZ_PWM: U201.4 (IO4); also elsewhere on the board
EN_BK: U201.10 (IO17); also elsewhere on the board
EN_BL: U201.23 (IO21); also elsewhere on the board
EN_BR: U201.21 (IO13); also elsewhere on the board
EN_ST: U201.19 (IO11); also elsewhere on the board
EN_SW: U201.8 (IO15); also elsewhere on the board
EN_TL: U201.28 (IO35); also elsewhere on the board
EN_TR: U201.30 (IO37); also elsewhere on the board
EXP_RX: U201.35 (IO42); also elsewhere on the board
EXP_TX: U201.34 (IO41); also elsewhere on the board
GND: C201.2, C202.2, C203.2, C204.2, D201.1 (K), D202.1 (K), J201.A1 (GND), J201.A12 (GND), J201.B1 (GND), J201.B12 (GND), J201.S1 (SHIELD), R203.2, R204.2, R208.2, SW201.2, SW202.2, U201.1 (GND), U201.40 (GND), U201.41 (GND), U202.2 (GND); also elsewhere on the board
ISNS_BK: U201.6 (IO6); also elsewhere on the board
ISNS_BL: U201.18 (IO10); also elsewhere on the board
ISNS_BR: U201.17 (IO9); also elsewhere on the board
ISNS_ST: U201.15 (IO3); also elsewhere on the board
ISNS_SW: U201.5 (IO5); also elsewhere on the board
ISNS_TL: U201.39 (IO1); also elsewhere on the board
ISNS_TR: U201.38 (IO2); also elsewhere on the board
LAMP1_PWM: U201.26 (IO45); also elsewhere on the board
LAMP2_PWM: U201.16 (IO46); also elsewhere on the board
NFAULT: R207.2, TP203.1, U201.32 (IO39); also elsewhere on the board
NSLEEP: R208.1, TP204.1, U201.25 (IO48); also elsewhere on the board
unnamed: D201.2 (A), R205.2
unnamed: D202.2 (A), R206.2
unnamed: J201.A5 (CC1), R203.1
unnamed: J201.B5 (CC2), R204.1
unnamed: C203.1, R201.2, SW201.1, U201.3 (EN)
unnamed: R202.2, SW202.1, U201.27 (IO0)
PH_BK: U201.11 (IO18); also elsewhere on the board
PH_BL: U201.24 (IO47); also elsewhere on the board
PH_BR: U201.22 (IO14); also elsewhere on the board
PH_ST: U201.20 (IO12); also elsewhere on the board
PH_SW: U201.9 (IO16); also elsewhere on the board
PH_TL: U201.29 (IO36); also elsewhere on the board
PH_TR: U201.31 (IO38); also elsewhere on the board
VBAT_SNS: U201.12 (IO8); also elsewhere on the board
VBUS: C204.1, J201.A4 (VBUS), J201.A9 (VBUS), J201.B4 (VBUS), J201.B9 (VBUS), U202.5 (VBUS); also elsewhere on the board

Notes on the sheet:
ESP32-S3-WROOM-1-N8 (no PSRAM, so GPIO35-37 are free), native USB, indicators
Straps: GPIO0 pulled up (hold BOOT at reset for download mode). GPIO45/46 held low by the lamp gate pull-downs (VDD_SPI 3.3 V, SPI boot). GPIO3 (JTAG strap) is ignored with the default eFuse. Analog inputs on ADC1 only: GPIO1, 2, 3, 5, 6, 9, 10 driver currents, GPIO8 battery. Enables and nSLEEP avo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
RESET
BOOT
USB-C device (flashing, logs): 5.1k on CC1 and CC2; both D+/D- pairs joined; USBLC6 ESD array.
Status LED (GPIO40), power LED, shared driver fault pull-up, sleep pull-down, UART0 test pads.
